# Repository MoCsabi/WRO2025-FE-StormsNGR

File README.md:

# Introduction
We are the StormsNGR team from Hungary, and we competed in the 2025 WRO Future Engineers category. This was our second year competing after a very successful first year, for which you can find our documentation [here](https://github.com/MoCsabi/WRO2024-FE-StormsNGR). We will be keeping that repository as it is, and will be updating this repository for the 2025 season.

# Results
We once again managed to earn a spot on the podium with 3rd place, a result we are very proud of 😊. We will be keeping this repository as is to help those who are interested study our complete 2025 season solution. For the 2026 season you can follow our progress in the [WRO2026-FE-StormsNGR](https://github.com/MoCsabi/WRO2026-FE-StormsNGR) repository.

## The team
>Team members
- **Csaba Molnár** from [Budapest University of Technology and Economics](https://www.bme.hu/en) Faculty of Electrical Engineering and Informatics
  - csabi@molnarnet.hu
- **András Gräff** from [Budapest University of Technology and Economics](https://www.bme.hu/en) Faculty of Mechanical Engineering
  - andrasgraff@gmail.com
- **Levente Molnár** from [Sóskút Károly Andreetti elementary school](https://iskola.soskut.hu/)
  - levente@molnarnet.hu
>Coach
- József Balázs Gräff
  - graffjozsefb@gmail.com

Links to our socials:

- **Facebook**: https://www.facebook.com/stormsteam/
  - Here you can find updates about the team
- **YouTube**: https://www.youtube.com/channel/UCyzm_Su7qoRCof-ZpbG_9Ig
  - Here you can watch videos about past competitions
- **Instagram**: https://www.instagram.com/storms_team_hun/
  - Cool posts and updates about our, and our sister-team StormsRMS' preparation for upcoming competitions

# Abstract
Our solution is an autonomous car powered by a Raspberry Pi coded in Python, responsible for the main challenge logic, and an ESP microcontroller coded in C, responsible for controlling the motors and processing sensor data. The two devices communicate using UART. We use a 360° 2D LiDAR combined with a gyro to always know where the robot is on the mat. Detection of the traffic sign's color is done by combining the output of the LiDAR with the camera feed to know exactly where the object is. We use ackermann steering geometry calibrated so the car can leave the parking space in one continuous arc. Driving is powered by 1 DC motor through a differential gearbox designed from scratch, with a top speed of around 2.6 m/s.

# Table of contents

### [Our journey](/Our%20Journey.md)
### [Ideas and principles](/Ideas_and_principles.md)
### [Hardware documentation](/schemes/README.md)
### [Software documentation](/src/README.md)
### [measurement- The robot's mechanical characteristics](/The%20robot's%20mechanical%20characteristics.md)
### [RpiCode development tool documentation](/other/README.md)
### [Videos](/video/video.md)
### [Team Photos](/t-photos/)
### [Vehicle Photos](/v-photos/)

# Special thanks
Special thanks to Zsolt Molnár for all the mentoring he's done for us, József Molnár from the [Budapest University of Technology and Economics](https://www.bme.hu/) Faculty of Mechanical Engineering for helping us with the preparations, György Fenyvesi for helping us develop our prototype [custom made interconnect panel](/schemes/README.md/#custom-made-interconnect-panel-wiring-with-connections-labeled), and a bunch of others for helping us by reviewing all the documentation. And of course, to both our families for tolerating us taking up the entire living room with the robot mat 🙂.

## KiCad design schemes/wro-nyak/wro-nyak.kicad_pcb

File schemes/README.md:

# Hardware documentation and setup guide
The robot is made up of a lot of different sensors, motors and two processing units, the ESP microcontroller and a Raspberry Pi. The car uses ackermann steering geometry and one DC motor through a motor controller with a differential gearbox we designed and printed from scratch. We had to create a lot of custom 3D printed components and even a custom interconnect panel to help with complicated wiring. The power to the robot is supplied by a 11.1V lithium battery and is later converted to 5V by a step-down module.

## List of components
We installed a lot of sensors and other components on the car, here is a list of each of them with a link and some additional notes:
- **Ackermann steering mechanism** and **base plates** [Ackermann Intelligent Car](https://www.hiwonder.com/collections/robotic-car/products/ackermann-steering-chassis?variant=40382428381271)
  - originally 270 x 197 mm, 960 g
- **Steering servo** [Carson CS-3](https://www.amazon.co.uk/Carson-500502015-500502015-CS-3-Servo-3Kg-JR/dp/B0037Y93CW)
  - Operating voltage 4.8 - 6 V, torque 31 Ncm, operating time 0.17 sec/60° dimensions : 38.5 x 19 x 32 mm, weight: 39 g
- **DC motor** [Hiwonder JGB37-520R30-12](https://www.hiwonder.com/products/hall-encoder-dc-geared-motor)
  -  Operating voltage 12V, torque 15 kg*cm max 3.2A, 280 RPM, 440 pulse-per-revolution encoder
- **Single Board Computer** [Raspberry Pi 5 4GB](https://www.raspberrypi.com/products/raspberry-pi-5/?variant=raspberry-pi-5-4gb)
  - Operating voltage 5V/5A USB-C, 4 USB ports, 40 pins
- **Microcontroller (ESP)** [NodeMCU-32S](https://www.hestore.hu/prod_10037961.html)
  - Operating voltage 5V, 2*19 pins, dimensions: 49.5 x 26 mm
- **Custom interconnect board**
  - ESP pins insert into this, PCB that groups common pins near each other, helps with wiring
- Inertial Measurement Unit (**IMU**/**Gyro**) [BNO085](https://www.hestore.hu/prod_10044901.html)
  - Operating voltage 3.3V, drift 0.5°/min, dynamic rotation error 4.5°
- **Motor driver** [DRV8871-MK](https://www.hestore.hu/prod_10048030.html)
  - Output 3.6 A max
- **Step-down module** [XL4015-3D-STDN-PSU](https://www.hestore.hu/prod_10042112.html)
  - Output 5V/5A, displays voltage, useful for checking battery state
- **Battery**
  - Bundled with Ackermann Intelligent Car, 11.1V, 6000mAh, lithium
- **Display and buttons panel** [Led&Key](https://www.hestore.hu/prod_10042203.html)
  - 8 seven segment displays, buttons, LEDs
- **Active buzzer** [Z2 buzzer (KPI-G2330E)](https://www.hestore.hu/prod_10029469.html)
  - Operating voltage 3-24V DC, 3700 Hz, 83 dB, dimensions ⌀23x10mm
- **Power switch** [ST 1/BK (MRS-1)](https://www.hestore.hu/prod_10023322.html)
  - Dimensions 19.3x12.9mm
- **LiDAR sensor** [STL-19P, D500 development kit](https://www.waveshare.com/wiki/D500_LiDAR_Kit)
  - Dimensions 38.6 x 38.6 x 34.8 mm, range 0.02-12 m, frequency 5-15 Hz, accuracy ±45 mm
- **Camera** [Raspberry Pi Camera Module 3](https://www.raspberrypi.com/products/camera-module-3/)
  - FPC connector, standard lens, RAW10 color format, vertical FOV up to 41°, horizontal up to 66°
- **Ball bearings**
  - 3 pieces of 7(inner diameter)x19x6 mm and 1 piece of 6(inner diameter)x12x4 mm
- **USB-TTL bridge** [CH341T-V3-M](https://www.hestore.hu/prod_10044421.html)
  - supports both 3.3V and 5V, enables us to use another serial port on the Pi for UART communication
- [**Carbon fiber Lego technic axle**](https://joooooy.com/products/moc-carbon-fiber-technic-axle-4519-3705-32073-3706)
  - can be cut to size, heavy-duty, won't bend as easily
## Assembly - Overview

This section serves as an overview of the design philosophy of the robot. For more details about the actual driving and steering mechanism see [Drive](#drive), and for building instructions see [Building instructions](#building-instructions).

Our robot utilizes ackermann steering geometry and differential drive. We have 3 decks, a bottom deck (or lower deck) for the servo, driving mechanism and the power supply. On the middle deck we have the Raspberry Pi, the main control unit coded in python, responsible for the main challenge logic, and the ESP microcontroller, the secondary control unit coded in C, responsible for receiving sensor data and controlling the motors. The LiDAR sensor is is also mounted here. The third deck is about half the size of the other decks, it houses things like the motor driver, the IMU, the display panel and the step-down PSU.
 
(Sketch that illustrates the connections between the different components of the robot)

For steering we used a solution that can be found in many RC cars, we took one from the Ackermann Intelligent Car by HiWonder. After calibrating the geometry to the length of our car we maximalized the steering range to ensure tight turns. We also replaced the steering servo for one with less power consumption and slightly smaller size. For the driving motor we used a 1:10 ratio 12V DC motor and secured it with 90° mounting brackets. The D-shaft of the motor goes inside the custom-designed differential gearbox, where we convert to a lego technic X axle, on which the wheels are mounted. For the rear wheels we used thin Lego wheels, and for the front wheels thin Lego compatible custom 3D printed wheels to make the robot less wide, and make parking easier. Due to the many heavy installments, such as the motor and the power supply, the center of gravity is low, which is ideal for track stability and turning.<br> On the middle deck we have the Raspberry Pi and the ESP-32 microcontroller with its pins mounted on a custom interconnect PCB. It helps with the wiring by routing certain pins next to each other and allowing us to use ribbon cables, making everything much cleaner. This deck is separated from heavy-duty equipment like the motor which cause electrical noise that could interfere with the controllers. The LiDAR sensor is also mounted here with a special mounting bracket, ensuring the widest FOV possible. The base of the camera tower is also mounted here.<br>The third deck is much smaller, the main reason we installed it was the lack of space for the remaining components, while also keeping the car small and light. Importantly the Led&Key input and display panel is also installed here for easy access. The camera tower ensures the camera is looking in front of the robot with a 15° vertical tilt down. The final size of the robot is 26.8 cm long, 15.8 cm wide and 20.9 cm high. It weighs 1246 grams.

## Wiring diagrams
The colored squares represent the cable colors on the robot.
### ESP microcontroller (NodeMCU) pinout with connections labeled:
This illustration is most important for the source code, since everything is actually wired through the custom-made board for the ESP.

(ENC-Motor encoder, PI-Raspberry Pi, D: directly connected, !: not wired through the interconnect panel)

### Raspberry Pi pinout with connections labeled:

(L&K-Led and Key panel)
### Motor controller wiring:

All of these can also be found in the form of an excel spreadsheet in the [pinouts.xlsx](pinouts.xlsx) document.

### Custom interconnect PCB schematic and wiring:

*Note: the red wires are on the top, the blue ones are on the bottom of the PCB, which let us connect everything in a clear, simple matrix layout without collisions*

Some extra rules had to be employed in order to ensure the PCB working properly. First, the GND and +3V3 as well as +5V wires were thickened, since they deliver much more current than everything else. Another big factor was the 5V wiring itself: the ESP could either get its 5 volt power through the built in pin or USB-C port, but not both without that causing issues (for example, it managed to break the USB port of two of our ESP-s). Because of this, a jumper bridge has been added, if the `ESP32 5V SWITCH` pins are not connected, the ESP must be supplied through the USB port, otherwise power delivery is done through the dedicated pin.

The PCB project, along with its BOM can be found in the [schemes/wro_nyak](/schemes/wro-nyak/) subfolder.

## Power
The robot's power supply is provided by a central accumulator (battery).
We considered powering the motors and the control system from separate power sources due to their differing requirements and to limit the electrical interference (noise), but ultimately decided on a common power source for simplicity. The 11.1 V, 6000 mAh lithium accumulator provides more than sufficient capacity for us. A lower capacity device would have also sufficed and while being lighter, but the ability to avoid constant recharging is a great advantage for us during the testing periods. For safety, the accumulator is easily removable via a detachable cable. We have a spare unit, enabling us to charge one while using the other. The accumulator connects directly to the main switch via the detachable cable.
The battery's largest consumer is the drive motor. The DC motor connects to the motor driver without voltage conversion. The driver's maximum current is 3.6A, which is sufficient for the motor's maximum current draw of 3.2A. The motor driver includes essential integrated protections (Overcurrent Protection - OCP, Thermal Shutdown - TSD).
The remaining components of the system operate at 5V, which we provide using a step-down power supply. A very useful feature of this power supply is that it displays the input voltage, allowing us to monitor the battery's state of charge. Among the 5V components, the Servo and the Raspberry Pi require significant current, which is handled by the power supply's 5A maximum current output.
A few of the robot's components, mainly sensors, operate at a 3.3V voltage level, but their power supply is provided by the controller (ESP/Pi) they are connected to.

A simple explanation of the power supply hierarchy of our robot.
- Battery `12V`
  - Step-down module `12V-->5V`
    - Steering servo `5V`
    - Raspberry Pi 5 `5V` (from USB-C, can supply `3.3V`)
      - LiDAR `5V`, **180mA**
      - Camera `5V` **200mA** (FFC)
      - Led&Key Panel `3.3V`
    - NodeMCU-32S `5V` (from **Vin** pin, can supply `3.3V`)
      - Inertial Measurement Unit `3.3V`
      - Motor encoder `3.3V`
  - Motor driver `12V`
    - DC motor `12V` **~1A**, max 3.2A

## Connections
The different connections used between the components of the robot and their hierarchy:
- Computer
  - Raspberry Pi `SSH`
    - ESP `UART` Pi: **USB-TTL** - ESP: **RXD-GPIO-25, TXD-GPIO-26**
      - IMU `UART-RVC` **(SDA-GPIO 17)**
      - Motor encoder `Digital` **(A-GPIO 34, B-GPIO 35)**
      - Motor driver 2x`PWM` **(PWM_1-GPIO 13, PWM_2-GPIO 16)**
      - Servo `PWM` **(Signal-GPIO 27)**
    - LiDAR `UART` **(TX-GPIO 15)** 
    - Led&Key panel `Data, Strobe, Clock` **(DIO-GPIO 19, STB-GPIO 16, CLK-GPIO 13)**
    - Buzzer `Digital` **(+-GPIO 5)**
    - Camera `FFC`

The actual communication between the components is detailed in the [software documentation](/src/README.md#sensors-and-motors).
## Drive
For steering, we utilize Ackerman steering geometry.
In short, the inner wheel turn slightly more than the other, so the robot stays on the same arc without any slippage. Here's an image from the [Hiwonder documentation](https://drive.google.com/drive/folders/11k0gbcZExI4076KJ1d_CCIdDlopuYUwO) that illustrates the principle:

The steering mechanism has to be assembled so the steering pivots are on the line between the steering kingpin and the center of the rear axle.

We use two kinds of turning, turning along an arc or turning until a target degree is reached using **PID** control with the gyro. For turning along an arc we can use this formula to calculate the correct servo angle for an arc given $R$ radius:
$$θ=arctan \left( {H \over R} \right)$$
($H$-distance between front and rear axles, $R$-target radius)

For driving we wanted to use [Electronic Differential](https://en.wikipedia.org/wiki/Electronic_differential), which is simply simulating a differential using software by calculating the required force using the current angle of the servo.
The formula for calculating the correct speeds of the two motors:
$${V_l}=\frac V R*\left( R-\frac D 2 \right)$$
$${V_r}=\frac V R*\left( R+\frac D 2 \right)$$

($V_l$- left motor speed, $V_r$- right motor speed, $R$- current arc, $V$- robot tangential speed)

This would have been the most ideal solution, as this way we could avoid complicated hardware components and also use the power of 2 DC motors easily. This is also how many modern real life electric cars operate (such as the [Tesla Model S](https://en.wikipedia.org/wiki/Tesla_Model_S#Powertrain) for example), and since the competition's main goal with car restrictions seem to be realism we hoped this solution would be accepted. However, with the reasoning that cheating by not accurately simulating a differential would be hard to detect, this solution was not allowed by the head judges. This way we had to design and 3D print a differential gearbox from scratch, and only use 1 DC motor. 

First, we created a mechatronic model of the drivetrain starting from the motor to the wheels.
The so-called mechanical impedances of the components ($Z_{force} = \frac{1}{m\cdot s}, Z_{torque}=\frac{1}{J\cdot s}$ in the Laplace domain)

From this, using a Jupyter notebook, all the parameters of the system could be calculated.
The moments of inertia were generated using the `numpy-stl` library, the rest were of the values were measured manually. From this we concluded that with the current setup the transmission ratio should be changed as much as possible to favor lower torques and higher rpm. We designed two helix gears with 1:1 transmission with Lego technic axle slots for heavy duty carbon fiber axles, which gave us more than enough maximum speed at 2.6 m/s. We made sure to use ball bearings where the axles are supposed to rotate freely. The design process is further detailed in [The design process of 3D printed parts](#the-design-process-of-3d-printed-parts). A simple diagram showing this solution:

($M$- DC Motor)

# The design process of 3D printed parts

Designing and printing out different parts of the robot was one of our biggest task where we had to take a lot of things into account in order **for everything to work properly**. Sometimes we had to rely on **trial and error** to make sure everything was how we wanted it to be.

---

## The steps of The design process:

### 1. Coming up with the general shape and location of the part
  
  In This part we first had to take a close look at how our robot looked so far then try to figure out **how and where our soon to be designed part could fit.**
  Things we had to look out for:
  - Having an appropriate amount of space for the parts.
  - Having the right screw holes to be able to make a good mounting mechanism.
  - Making sure that putting the part there wouldn't interfere with anything else.
  
  After we found to correct location we made a very, **very simplistic sketch** of what we wanted.

### 2. Gathering usable documentation
  This is maybe the most important part in the process, because the quality of the documentation available **can make or break a design**. While taking your own measurements is viable, it is a lot simpler to use a documentation and yields **more precise results**.

### 3. Making the model
  We used *Autodesk Fusion 360* for designing our parts, however any industrial software like *Autodesk Inventor* can be used as well. In the modelling process there are a couple of things to remember:
  
  - Make sure that any measurement given in a documentation seems realistic, **since we have seen mistakes even in official documentations**.
  - Always double check any calculation and check the dimensions relative to multiple sides, because **it may look alright from one side, but may be completely unusable from another**.
  - Use your software's built in physics simulators to check for weak points and **always make sure it can handle the stress it may be placed under**.
  - When done export the file as an **.stl** so that a slicer can use it.

  Don't worry if you don't know how to make 3D models yet, it is a lot easier than people might think. The process in simple terms just requires you to make a sketch/blueprint like below and extrude it out into 3D space.

### 4. Exporting the G-code
  We printed our parts with a *PRUSA mini+* and used *PrusaSlicer*, but any 3D printer and software will do as long as it has a **large enough print area** and supports the **right types of filament** (we use PLA but PETG should also work). We suggest that for more **aesthetic parts a 30% infill** is used and for **more structural ones a 60%**. It may also seem trivial but the **angle and orientation** in which the part is printed matters a lot to. For example **for tires a $45°$ tilt** is suggested to make sure that it **won't come apart parallel to the print lines.**

### 5. Printing out the part
  Here there is not much to look out for, just make sure that the **printer's settings are right,** there is enough filament and the **supports are sufficient.**

---

## How we applied these steps and the difficulties we faced

### The lidar mount

  The lidar mount was the *first part* which we designed ourselves and the part that makes it so that the lidar can see **exactly what we want it to see.** While the robot chassis had the right screw holes to mount it to begin with, the problem we faced relied on the angle in which the lidar shoots out its beams of light. It was slightly angled to shoot upwards. Because of this the lidar was **seeing above the walls** of the map which was a lot less than optimal. Our solution was to flip the lidar upside down to **lower the starting point of the beams and make them shoot slightly downwards instead.**
  The main things we had to look out for in this part were:
  
  > **Making sure that it won't start tilting in random directions throughout the round.**
  
  The way we solved this was, that the mount just makes it so that it doesn't move horizontally, but vertically it doesn't give much support, **letting it lie directly flat on the vehicle**.

  > **Mounting it securely while leaving enough space for a wide field of view.**

  We solved this by only mounting it from the back with two screws, which does give up a lot of stability, but we **still found it sufficient for this use case**.

  > **Making the range of the Lidar as wide as possible while also allowing it to see backwards**

  This was the easiest since we just had to have an empty slot in the back of the mount.

  [The documentation we used (Page 7 is the most important)](https://www.ldrobot.com/images/2023/05/23/LDROBOT_LD19_Datasheet_EN_v2.6_Q1JXIRVq.pdf)

  This part worked flawlessly so we have been using it ever since last year's competition.

### The camera stand
  
  The camera stand was one of the parts that needed an almost complete redesign over last year, but this time it did not require four iterations to get the final result.
  The mounting area stayed the same, using two screws for security and having the main body elevated in order to **allow the Lidar's laser to pass through below it.**
  The top part however required a complete redesign since we changed cameras. It needed to keep the camera at a **height of 20 cm with a depression angle of 15°** to get the correct image. This made the piece quite tall, so a few security bars were added for support. To mount the camera we made small pins that fit exactly into the screw holes of the camera. To make it so that it doesn't fall out, a lid can be slotted in from the top. Between the lid and the camera we also inserted a few pieces of paper to cushion it and make sure nothing gets damaged.

  [The blueprint we used](https://datasheets.raspberrypi.com/camera/camera-module-3-wide-mechanical-drawing.pdf)
  [Link to previous year's version](https://github.com/MoCsabi/WRO2024-FE-StormsNGR/blob/main/schemes/README.md#the-camera-stand)

  The lid is as simple as this, so it doesn't even need to be 3D printed, a piece of cardboard would work just as fine.

### The tunnel
  We adjusted the lidar mount and camera stand to enable the **lidar to see backwards,** however another part was needed to be designed to make sure that **nothing obstructed the view.** This was the most simple model we ever made, since it really is just a **little tunnel** meant to clear the way.

  It is mounted using four screw, which is a bit of an **overkill,** since realistically it won't really be put under any stress. Because of this we only ended up putting screws into the two rear holes.

### The differential gear
  This year we decided to make a custom differential and replace the old Lego one. This model required by far the most engineering knowledge.
  The differential was designed with a few important factors considered:
  >-  **To have a size similar to the previous so it would be easier to implement into the assembly.**
  >-  **To have enough tolerances for 3D printing, but at the same time to minimize the backlash between the various gears and - of course - to achieve maximum efficiency.**

  In order to achieve this, we decided to use two helical gears, with one replacing the gear part of the old differential, while not changing the rest. The helical gears allow for better contact between the gears, and therefore a **higher efficiency when the car goes forwards.** Size wise both gears are the same size now (due to the 1:1 gear ratio), their diameters are about equal to the bigger gear in the old differential, so the main axle could stay almost identical to before, with only the motor's position changing slightly.

### The differential gear frame
  With a new differential we also required a new frame for said differential. The frame is what holds differential in the air so that it doesn't touch anything, and **has embedded bearings to reduce the friction** between the frame and the axles. We used bearings last year as well but this year we made a few improvements in that area.

  >- **Made the slots larger that can accompany larger bearings that provide more support and enables the usage of fitting rings on the axles.**
  >- **Split the model into two and added walls for the slots to make the bearings and the fitting rings unable to move.**

  These changes made the frame a lot more secure, since we had problems with the bearings and axles shifting previously.

  [Link to previous year's version](https://github.com/MoCsabi/WRO2024-FE-StormsNGR/blob/main/schemes/README.md#the-differential-gear-frame)

### The assembly of the full differential gear

### Accessories for the differential gear

  The differential gear and house works as is just fine, but for our use case we needed a few extras for it.

#### The fitting rings

  As mentioned above, the axles we used required fitting rings in order to fit cleanly into the bearings. The rings then were glued onto the axles, since the frame restricts the movement of the ring, this makes it that the **entire axle can only be moved if the frame itself is disassembled.**

#### The axle holder

  In our robot the differential was on the right side, one of the axles needed to be exceptionally long which would enlarge any potential bending. To counter this we made a securing device which is basically just a box with a bearing in it. Just like the frame, **this was also split in two,** but since this part is completely symmetrical, it only requires one model.

### The new wheel

As mentioned before, to save parking space, we decided to switch to thinner wheels, but that caused problems on the front, when mounting. To fix this, we found an STL file of the rims we used online and modified it. We only made two small adjustments.

>- **We filled the axle hole in the middle of the wheel and inserted a circular hole that an M4 screw can fit through.**
>- **Addded a hexagonal indent to the outside which can fit an M4 nut.**

Applying these adjustments made the mounting of the front wheels a lot more secure, and also made them take a more straight path on the road, whereas before, there was a slight wobble when going straight.

### Aesthetic pieces

To make our robot fit its name **Dózer** a lot better, we made a few design parts for it as well.

---

## Conclusion
  
  Designing custom 3D printed parts is hard and while sometimes we can get lucky, like with the lidar mount, **other times it may take a long time and multiple versions until we get it right.** The step by step guide was written according to the **things we learned during our process and things we will be doing in the future.** Making sure that a design is good can be one of the most important steps during the entire process of making a robot. It is of the utmost importance to ensure that **the amazing software one might have doesn't get bottlenecked by bad parts.**

# Building instructions
The 3 decks of our robots are based on the decks from the HiWonder Ackermann Intelligent Car, but you could use any material. Screwholes won't be a problem either, just note the critical measurements and drill them yourself!

First we sawed off parts of the bottom and top decks, as can be seen on this sketch:

Then we repurposed the top deck's rear sawed off part as the third deck.

These decks can be mounted on each other with large spacers. The steering mechanism we used from the Ackermann Intelligent Car also plays a role in the structural integrity of the robot.

On the bottom deck we have the aforementioned steering mechanism, differential gearbox, the motor and the battery. How the differential gear-system is made up is detailed in the [Drive](#drive) and [The design process of 3D printed parts](#the-design-process-of-3D-printed-parts) sections. The motor has to be secured down, for this we used the original motor mounting bracket. The battery's position is not important as long as its secured down. This decks intentionally contains most of the heaviest components (the motor and the battery) in order to keep the center of gravity low.

The middle deck contains the main computing units of the robot, the Raspberry Pi and the ESP microcontroller with the custom-made interconnect panel. It also houses the gyro and the LiDAR sensor, which has to be placed right on the front of the deck, upside down, as secured down with our custom 3D printed LiDAR bracket and ideally supplied with an at least a 230° vision free from any blocking elements. Under the Raspberry Pi is our 3D printed tunnel piece, which has to be installed in a way that both ensures backwards vision to the LiDAR, free from any interfering objects, such as loose cables, and also acts as a support for the Pi and the ESP board. The camera is also installed on this deck by 2 screws, behind the LiDAR. The buzzer can be fixed anywhere, we used a small strip of [3M Double Lock](https://www.3m.com/3M/en_US/dual-lock-reclosable-fasteners-us/) tape, so we can remove it if necessary.

The top deck is installed atop the middle deck by two screws and spacers. It's not suitable to support serious weight, but this is not a problem since the components on there are really light. It houses the motor controller, the step-down-module (PSU) and the Led&Key panel. For the PSU and the Led&Key it was important that they're installed somewhere visible since they have displays with important information, so the top deck was perfect for them. On the Led&Key there are also buttons, which we use to start the rounds, so it's really important that these are supported, since a lot of force is going to be affecting them from above(pressing). We solved this by supporting the buttons from below using spacers. The third deck has to be relatively lightweight to not raise the center of gravity too high.

All components have to be installed using small spacers to avoid contact with the metal decks. Wiring between components is done using jumper cables, or in some cases thicker power cables for 12V. For more details on the wiring refer to [Wiring diagrams](#wiring-diagrams).
## Conclusion
We had quite a few difficulties during the assembly and planning process, but we are very proud of our work. If there are any problems or further questions don't hesitate to contact us at csabi@molnarnet.hu (Csaba) or andrasgraff@gmail.com (András)

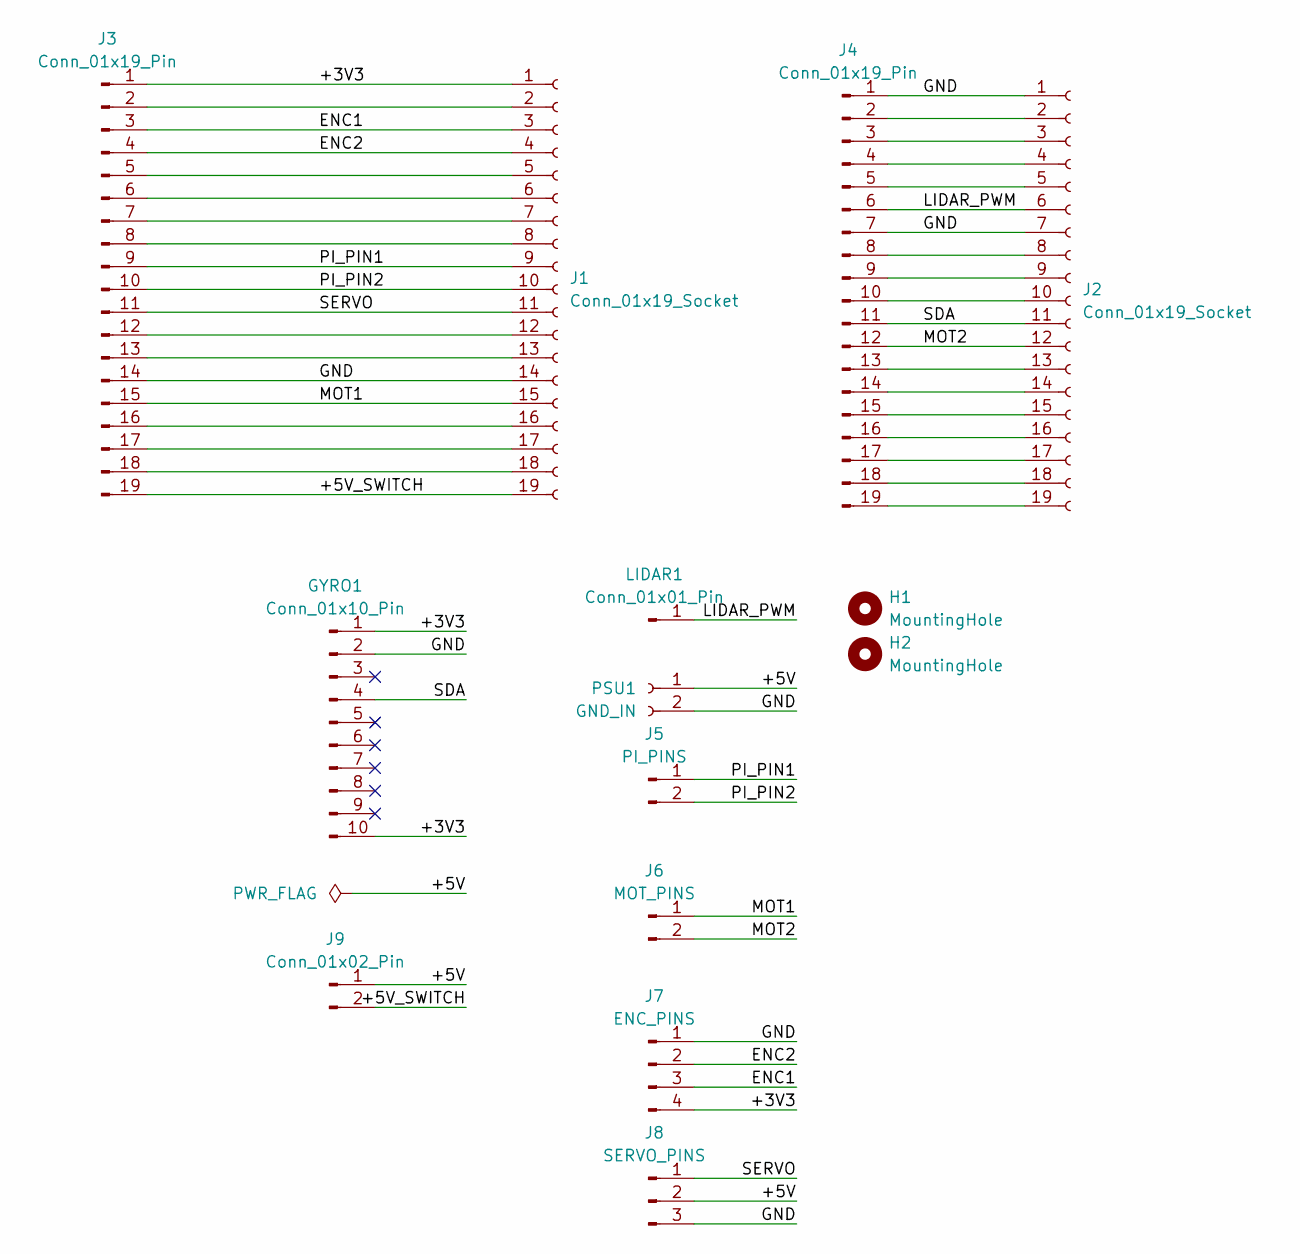
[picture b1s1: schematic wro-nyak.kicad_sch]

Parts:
GYRO1: Conn_01x10_Pin; PinSocket_1x10_P2.54mm_Vertical; LCSC C57369
H1, H2: MountingHole; MountingHole_3.2mm_M3
J1, J2: Conn_01x19_Socket; PinSocket_1x19_P2.54mm_Vertical; LCSC C2897382
J3, J4: Conn_01x19_Pin; PinSocket_1x19_P2.54mm_Vertical; LCSC C2897382
J5: PI_PINS; PinHeader_1x02_P2.54mm_Vertical; LCSC C2905434
J6: MOT_PINS; PinHeader_1x02_P2.54mm_Vertical; LCSC C2905434
J7: ENC_PINS; PinHeader_1x04_P2.54mm_Vertical; LCSC C2905435
J8: SERVO_PINS; PinHeader_1x03_P2.54mm_Vertical; LCSC C2932698
J9: Conn_01x02_Pin; PinHeader_1x02_P2.54mm_Vertical; LCSC C2905434
LIDAR1: Conn_01x01_Pin; PinHeader_1x01_P2.54mm_Vertical; LCSC C81276
PSU1: GND_IN; TerminalBlock_Xinya_XY308-2.54-2P_1x02_P2.54mm_Horizontal; LCSC C5188442

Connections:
/+3V3: GYRO1.1, GYRO1.10, J1.1, J3.1, J7.4
/+5V: J8.2, J9.1, PSU1.1
/+5V_SWITCH: J1.19, J3.19, J9.2
/ENC1: J1.3, J3.3, J7.3
/ENC2: J1.4, J3.4, J7.2
/GND: GYRO1.2, J1.14, J2.1, J2.7, J3.14, J4.1, J4.7, J7.1, J8.3, PSU1.2
/LIDAR_PWM: J2.6, J4.6, LIDAR1.1
/MOT1: J1.15, J3.15, J6.1
/MOT2: J2.12, J4.12, J6.2
/PI_PIN1: J1.9, J3.9, J5.1
/PI_PIN2: J1.10, J3.10, J5.2
/SDA: GYRO1.4, J2.11, J4.11
/SERVO: J1.11, J3.11, J8.1
unnamed: J1.2, J3.2
unnamed: J1.5, J3.5
unnamed: J1.6, J3.6
unnamed: J1.7, J3.7
unnamed: J1.8, J3.8
unnamed: J1.12, J3.12
unnamed: J1.13, J3.13
unnamed: J1.16, J3.16
unnamed: J1.17, J3.17
unnamed: J1.18, J3.18
unnamed: J2.2, J4.2
unnamed: J2.3, J4.3
unnamed: J2.4, J4.4
unnamed: J2.5, J4.5
unnamed: J2.8, J4.8
unnamed: J2.9, J4.9
unnamed: J2.10, J4.10
unnamed: J2.13, J4.13
unnamed: J2.14, J4.14
unnamed: J2.15, J4.15
unnamed: J2.16, J4.16
unnamed: J2.17, J4.17
unnamed: J2.18, J4.18
unnamed: J2.19, J4.19

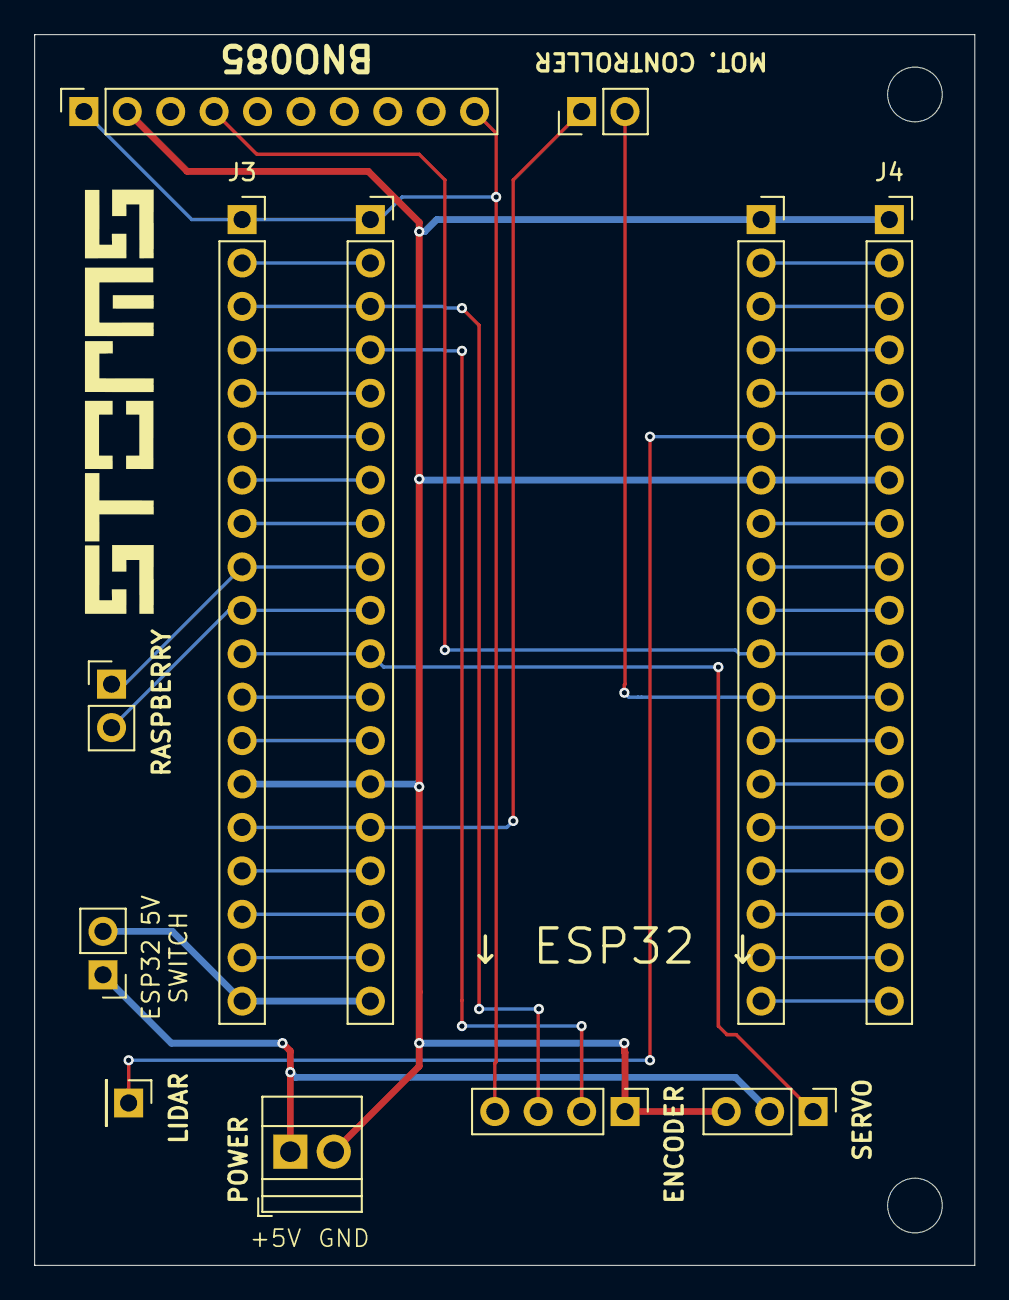
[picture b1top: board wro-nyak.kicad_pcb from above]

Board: 2 copper layers, 55.0 x 72.0 mm, 14 parts (0 on the bottom side), 37 nets.

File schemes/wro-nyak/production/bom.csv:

Designator,Footprint,Quantity,Value,LCSC Part #
GYRO1,PinSocket_1x10_P2.54mm_Vertical,1,Conn_01x10_Pin,C57369
"J1, J2",PinSocket_1x19_P2.54mm_Vertical,2,Conn_01x19_Socket,C2897382
"J3, J4",PinSocket_1x19_P2.54mm_Vertical,2,Conn_01x19_Pin,C2897382
J5,PinHeader_1x02_P2.54mm_Vertical,1,PI_PINS,C2905434
J6,PinHeader_1x02_P2.54mm_Vertical,1,MOT_PINS,C2905434
J7,PinHeader_1x04_P2.54mm_Vertical,1,ENC_PINS,C2905435
J8,PinHeader_1x03_P2.54mm_Vertical,1,SERVO_PINS,C2932698
J9,PinHeader_1x02_P2.54mm_Vertical,1,Conn_01x02_Pin,C2905434
LIDAR1,PinHeader_1x01_P2.54mm_Vertical,1,Conn_01x01_Pin,C81276
PSU1,TerminalBlock_Xinya_XY308-2.54-2P_1x02_P2.54mm_Horizontal,1,GND_IN,C5188442

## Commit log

2025-03-04 introduction added
2025-03-04 added template structure
2025-05-23 added up-to-date code
    includes switching to using a rapberry pi camera module instead of the pixy cam
2025-06-20 first draft of software documentation
2025-06-21 software documentation fixes
2025-06-21 formatting fixes, some new images
2025-06-23 first (wip) draft of hardware documentation
    some images are outdated, along the entire section of 3D printed parts
2025-06-23 minor fixes
2025-06-24 fixed side view diagram
2025-06-24 added ideas&principles, extansion documentation, team photos
    also fixed some documentation errors
2025-06-24 updated images and principles
2025-06-24 added vehicle photos and showcase videos
2025-06-24 Added our Journey
    still requires links to different parts
2025-06-24 added main readme
2025-06-24 Update README.md
    added middle name so that father and son will not be mixed up
2025-06-25 Update README.md
    updating the 3d prints section
2025-06-25 updating images for the 3D modells section
2025-06-25 Delete models directory
    deleting directory to wipe its content, going to readd it with the correct files
2025-06-25 Create README.md
    readding models
2025-06-25 Added the contents of the model directory
2025-06-25 spelling mistakes
2025-06-25 updated special thanks
2025-06-27 final version of code
2025-06-29 competition code uploaded
2025-11-05 2025+src docs
2025-11-06 updated main readme
2025-11-07 added photos
2025-11-07 our journey first draft
2025-11-07 adding images for our journey
2025-11-09 added video links and pseudo code
2025-11-10 updated illustartions, fixed documentation errors
2025-11-11 updated documentation
2025-11-14 added team photos
2025-11-14 Update README with PCB and wheel design details
    Added notes on PCB wiring and modifications to wheel design.
2025-11-14 Adding the files for the new wheels
2025-11-15 updated power documentation
2025-11-19 small mistake fixed
2025-11-23 added up-to-date code
2026-02-11 final commit
